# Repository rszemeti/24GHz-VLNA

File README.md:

# 24GHz-VLNA
24GHz VLNA

So, here are my thoughts on an LNA design for 24 GHz, inpired by Ron Schiltmans DU3T design, I thought I would try something similar.

The basic concept is a waveguide input, 2 stage desgin for 24GHz,  with a CE3520K3 FET on the input, and a MMIC amplifier as the second stage.  For the second stage I plan to use an HMC341 I will include my calculations and assumptions for the design, if you can spot an error in my thoughts, I would be of course, delighted to hear from you!

The circuitry on the left is a simple 3.3V regulator, feeding a ICL7660 negative voltage generator. The 3.3V is used to feed power to the MMIC amplifier and the input FET.  A simple P type FET prevents power being supplied to the front end FET before the negative voltage is present.

The  CE3520K3 was selected as it is pretty much the only real option easily obtainable from Mouser. I'd like to give you a better answer based on cost and performance, selection of matching parameters etc, but basically, it comes down to availability.

The matching data came from the datasheet for the input FET, which is handily provided by the manufacturer, complete with optimum reflection coefficients for best noise at 24GHz.

We can see that best noise figure is obtained with a reflection coefficent of 0.213/ -50.857 degrees presented to the input of the FET. Converting that reflection coefficient to a complex impedance we get  61.47 -j 21.27 Our goal in matching is to provide a circuit that transforms the (hopefully) 50 ohm input impedance to this complex impedance.  The tool of choice for this is SimSmith, the plot and matching circuit is shown below.

We can see that a length of 37 degrees of 71 Ohms of microstrip will perform the desired transformation. The width of the 50 Ohm and 71 Ohm strips was obtained from the Roger PCB calculator, for RO4003C in 0.508mm thickness.  The software also provides the velocity factor of 0.604 which is put back into SimSmith which produces a lenght of 0.78mm for the matching section. These elements are then inserted on the PCB directly before the input to the FET.

Using the usual equation for the output match:

I wrote a small program in Perl to perform the calculation. Feeding in the input reflection coefficient from above, and the S parameters from the datasheet:

I ran the program and got the output impedance of the FET first stage as follows:

I then fed the output impedance of 34.05 -j 37.47 ohms back into SimSmith and selected appropriate stripline elements to transform this to 50 ohms:

The two matching elements of 30 degrees of 75 Ohms and 90 degrees of 36 Ohms were selected and these were added to the ouput of the FET to transform the impedance to the 50 Ohms of the microstrip and the input of the second stage.

 I did not perform any analysis of stability criteria, I have seen it done, but as yet, it is above my pay grade.

The second stage has internal matching and isolation capacitors, so no additional input DC block is needed.  0402 sized resistors and bypass C's were selected, as these are about as small as I can reliably place by hand.

The input "window" is based on RG42 waveguide and flange sizing, the probe length is selected at 2.41mm and 1.27mm wide, this is from W1GHZ's SMA transition data, which gives a probe diameter of 1.27mm and a length of 2.41mm ...  handily, our 50 Ohm track is very close to 1.27mm  so no transition was needed ... 

The "backshort" will be machined into the aluminium casing for this PCB, 2.49mm is specified .. I'm going to place the board in the aluminium mount with the probe on the "short" side, and the open waveguide side seeing just the PTFE substrate. This should allow me to machine a 2.49mm deep section without having to take into account the velocity factor of the PTFE substrate. If the board is mounted with the probe nearest the open side, the RF has to pass theough the substrate to get to the "short", so an allowance would have to be made for the velocity factor of the PTFE.

Finally, we have the output filter and here I have to confess to what can only be described as guesswork. Much staring at similar filters, poking around in some 24GHz transverter modules with a set of vernier calipers and  similar foolish attempts were made ... in the end, I have no clue if it is close or not.   The "plan" is to obtain some RO4003C in the appropriate thickness and attempt to photo etch a filter and make a measurement with my signal generator and spectrum analyzer before buying 10 boards from a board house.

The basic layout is shown below:

Boards in RO4003C are not cheap, 10 boards will be around $350 which is "significant" when you have no real clue if they will work!  As a shoddy workaround, and just to check the mecahnics of it and any stupid "DC" type mistakes, I'll order a few boards in FR4, which naturally will be miles of in RF terms but will serve to check the basic board for errors before comitting to having some made in RO4003C. I may populate a board in FR4, just for fun ... well, for some values of fun anyway!

Datasheets:

HMC341 

CE3520K3 

Software:

SimSmith

Rogers MWI2019 (requires login)

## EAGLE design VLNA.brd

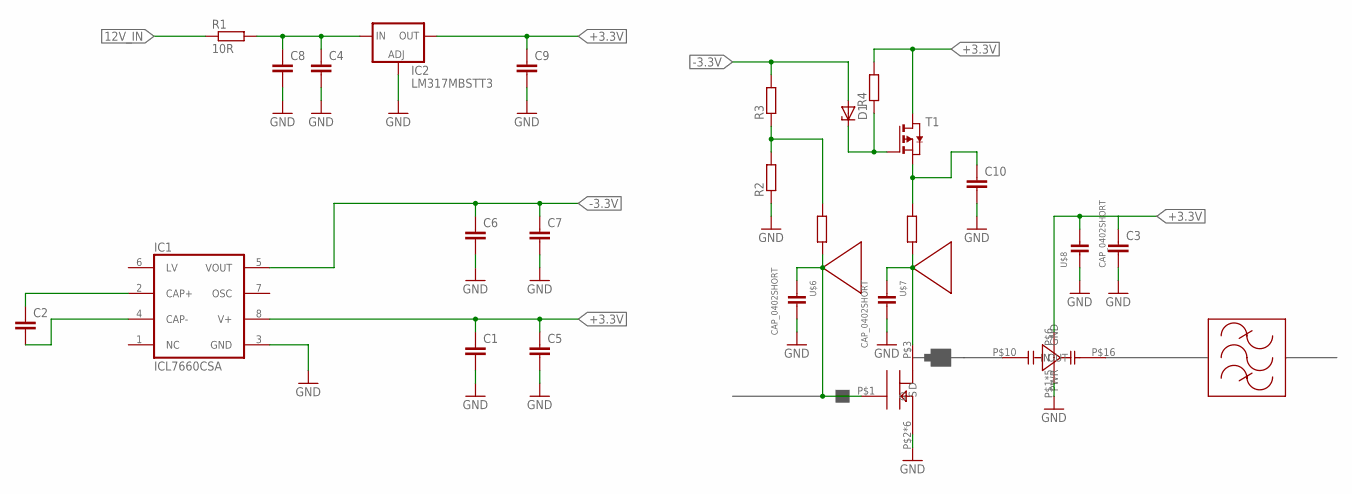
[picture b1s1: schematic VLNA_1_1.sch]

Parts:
C1, C2, C4, C5, C6, C7, C9, C10: C-EUC0603; C0603
C3: C-EUC0402; C0402
C8: C-EUC0805; C0805
D1: ZENER-DIODESOD80C; SOD80C
IC1: ICL7660CSA; SO08
IC2: LM317MBSTT3; SOT223
R1: 10R; R0805
R2, R3, R4: R-EU_R0603; R0603
T1: PMOSSOT23; SOT-23
U$2: 24GHZ_OP; FILTER
U$3: CE3520K3; MICROX
U$4: HMC341; HMC
U$5, U$9: RES_0402SHORT; 0402S
U$6, U$7, U$8: CAP_0402SHORT; 0402S
U$10, U$11: STUB; QTR_STUB

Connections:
12V_IN: R1.1
+3.3V: C1.1, C3.1, C5.1, C9.1, IC1.8 (V+), IC2.4 (OUT), R4.2, T1.1 (D), U$4.P$6 (PWR), U$8.P$2
-3.3V: C6.1, C7.1, D1.A, IC1.5 (VOUT), R3.2
GND: C1.2, C3.2, C4.2, C5.2, C6.2, C7.2, C8.2, C9.2, C10.2, IC1.3 (GND), IC2.1 (ADJ), R2.1, U$3.P$2 (S), U$3.P$4 (S), U$3.P$5 (S), U$3.P$6 (S), U$3.P$7 (S), U$3.P$8 (S), U$4.P$1 (GND), U$4.P$9 (GND), U$4.P$11 (GND), U$4.P$15 (GND), U$4.P$17 (GND), U$6.P$2, U$7.P$2, U$8.P$1
unnamed: C2.1, IC1.2 (CAP+)
unnamed: C2.2, IC1.4 (CAP-)
unnamed: C4.1, C8.1, IC2.3 (IN), R1.2
unnamed: R2.2, R3.1, U$5.P$2
unnamed: U$3.P$1 (G), U$5.P$1, U$6.P$1
unnamed: U$3.P$3 (D), U$7.P$1, U$9.P$1
unnamed: C10.1, T1.2 (S), U$9.P$2
unnamed: D1.C, R4.1, T1.3 (G)

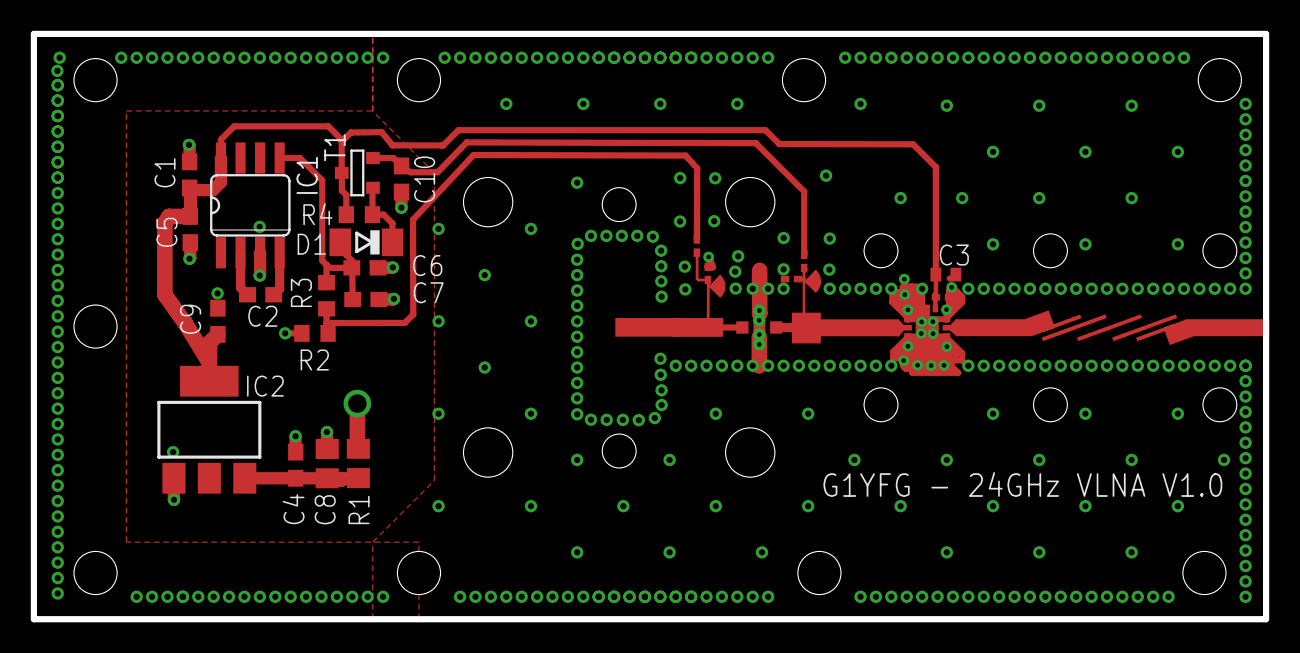
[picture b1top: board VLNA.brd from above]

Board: 2 copper layers, 80.0 x 38.0 mm, 29 parts (0 on the bottom side), 11 nets.

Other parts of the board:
U$1: FLANGE

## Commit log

2022-03-31 Initial Commit
    Initial commit, with reduced height WG input for a "stepped" transition to WR42
2022-03-31 Create README.md
    Copy/Paste of text from blog
2022-03-31 Hardware Files
    DXF and a Vectric Vcarve file for the top lid
2022-03-31 Create LICENSE
